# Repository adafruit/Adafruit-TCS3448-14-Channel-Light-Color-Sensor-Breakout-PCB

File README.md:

## Adafruit TCS3448 14-Channel Light / Color Sensor Breakout - STEMMA QT / Qwiic PCB

<a href="http://www.adafruit.com/products/6525"><br/>
Click here to purchase one from the Adafruit shop</a>

PCB files for the Adafruit TCS3448 14-Channel Light / Color Sensor Breakout - STEMMA QT / Qwiic. 

Format is EagleCAD schematic and board layout
* https://www.adafruit.com/product/6525

### Description

The <b>Adafruit TCS3448 (a.k.a TCS34488) Multi-Spectral Sensor</b> is a multi-channel spectrometer, which is a special type of light sensor that is able to detect not only the amount of light present but also the amounts of light within different wavelengths. This means that you can use it to detect much better than the human eye is capable of, what color or colors of light is present.

The TCS3448 packs within its 3x2mm footprint 25 photodiodes that can detect 11 separate, overlapping bands of visible light, plus one near infrared, one clear and a flicker channel for 14 channels total. Compared to the AS7341, this sensor has 4 more light channels - but you'll need to use a new firmware driver since it's not back-compatible.

<b>The TCS3448 is ams Osram's 'refresh' of the AS7343</b>, so it's an upgrade from the AS7341 and has some slight improvements/changes over the AS7343: 

* I2C address changed from 0x39 to 0x59.
* Retuned optical filters: channel centers move by a few nanometers and several visible channels have higher responsivity especially violet/blue and the F8 far-red channel.
* Sensitivity is not higher everywhere; NIR response is lower.
* Firmware is not 100% drop-in! You'll need to recompile since the I2C address has changed

The multi-spectral color measuring capabilities of the TCS3448 can be used to quantify the specific makeup of light, either emitted or reflective. It's kind of like a mini spectroscopy sensor. This is possible thanks to the impressive collection of sensors in the TCS3448 being routed through 6 independent 16-bit ADCs that take the raw measurements and convert them to digital values that can be read out over I2C.

14 readable individual sensor elements (13 light channels plus flicker detection) don’t exactly fit through a 6-channel ADC all at once, so the chip includes a so-called Super MUX (SMUX) that allows you to route the signal from any sensor to any ADC channel. The sensor also has GPIO and interrupt pins that can allow it to communicate directly with other sensors, or the microcontroller itself.

All of this capability is made accessible by mounting the sensor on a STEMMA QT form factor breakout board, complete with level shifting circuitry and [SparkFun Qwiic](https://www.sparkfun.com/qwiic) compatible [Stemma QT](https://learn.adafruit.com/introducing-adafruit-stemma-qt) connectors. This means that you can, without needing to solder, connect our TCS3448 breakout into your 3.3V or 5V microcontroller of choice be it an Arduino Uno, Raspberry Pi, or one of the many [CircuitPython-compatible boards](https://circuitpython.org/downloads). While it certainly takes a bit of work to make all those different light sensors share their measurements, our Arduino and CircuitPython libraries take care of all of that hard work for you and even include example code to help get you started. [QT Cable is not included, but we have a variety in the shop](https://www.adafruit.com/?q=stemma+qt+cable&sort=BestMatch).

### License

Adafruit invests time and resources providing this open source design, please support Adafruit and open-source hardware by purchasing products from [Adafruit](https://www.adafruit.com)!

Designed by Limor Fried/Ladyada for Adafruit Industries.

Creative Commons Attribution/Share-Alike, all text above must be included in any redistribution. 
See license.txt for additional details.

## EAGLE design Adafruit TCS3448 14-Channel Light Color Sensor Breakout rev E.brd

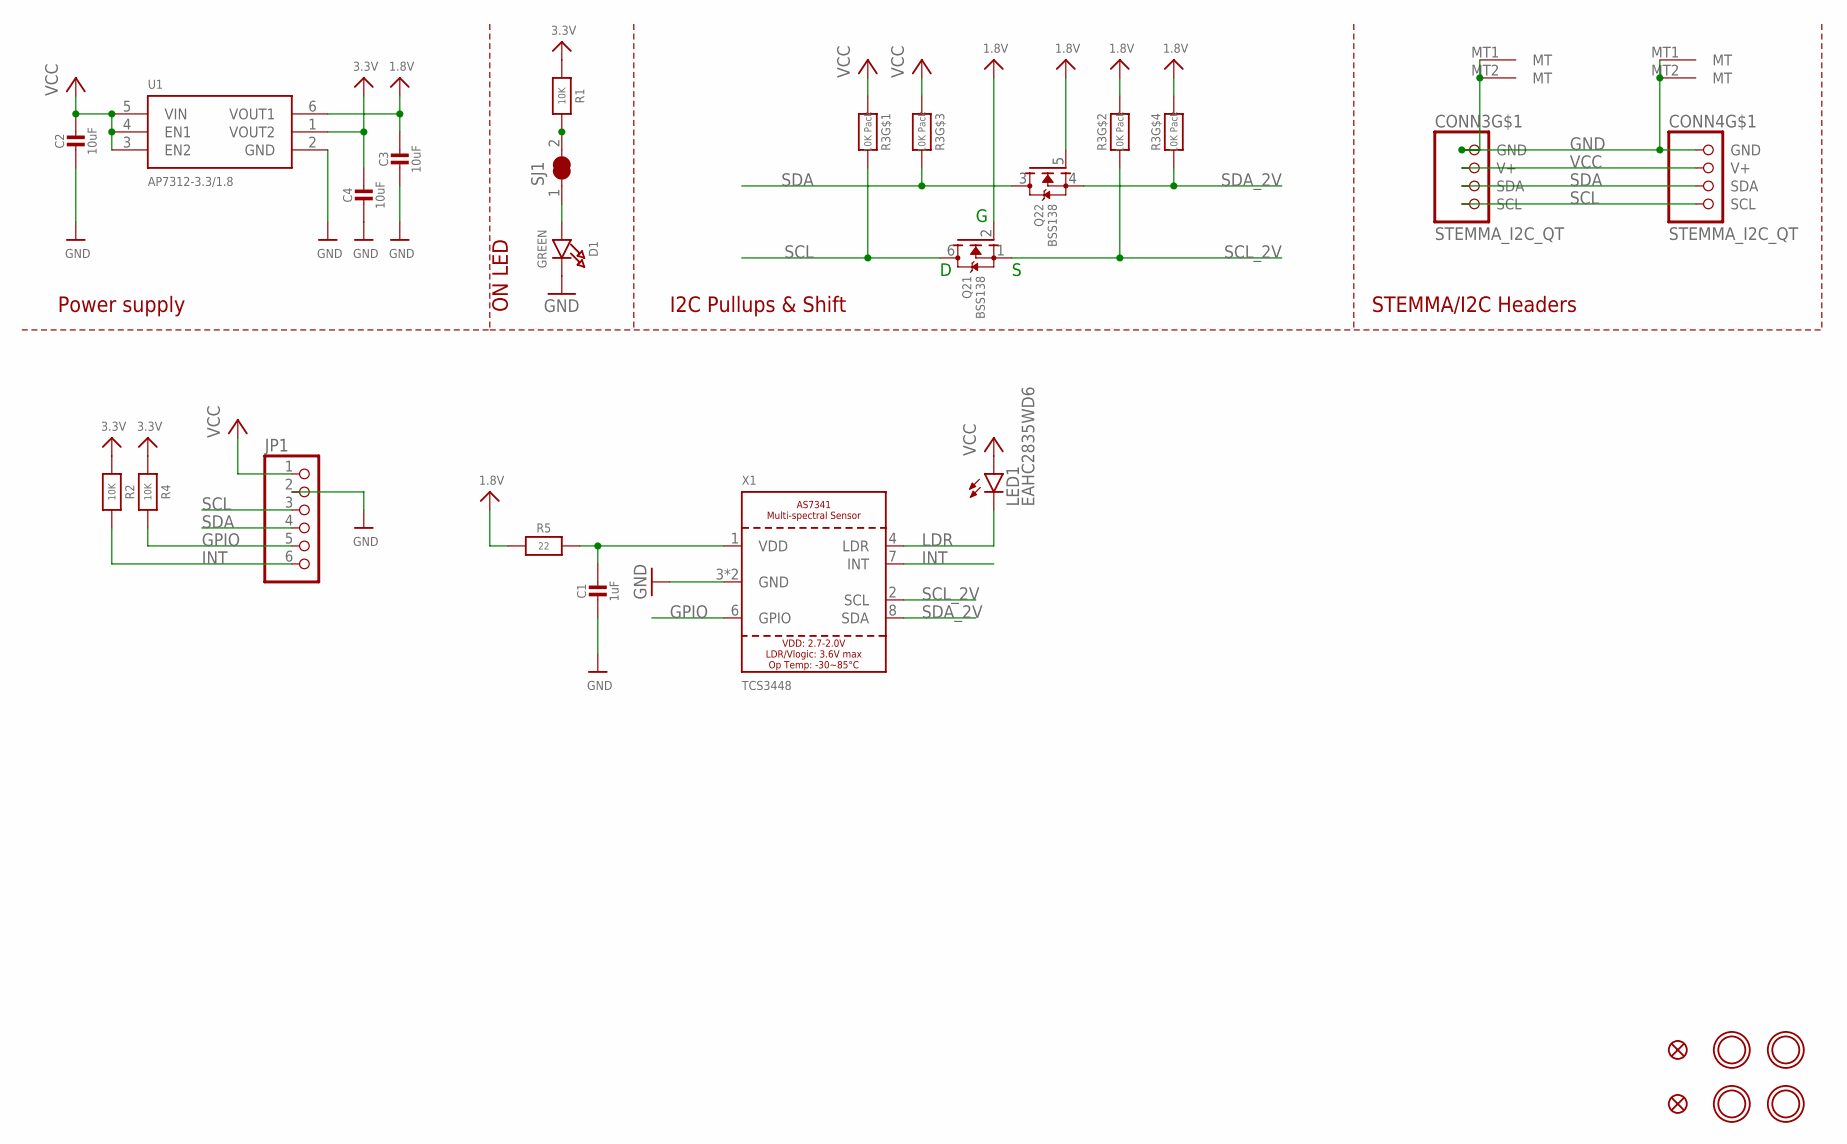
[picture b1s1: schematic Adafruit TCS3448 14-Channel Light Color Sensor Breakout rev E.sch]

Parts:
C1: 1uF; 0603-NO
C2, C3, C4: 10uF; 0805-NO
CONN3, CONN4: STEMMA_I2C_QT; JST_SH4
D1: GREEN; CHIPLED_0603_NOOUTLINE
FID3, FID4: FIDUCIAL_0.5MM
JP1: HEADER-1X670MIL; 1X06_ROUND_70
LED1: EAHC2835WD6; KA-3528ASYC
Q2: BSS138; SOT363
R1, R2, R4: 10K; 0603-NO
R3: 10K Pack; RESPACK_4X0603
R5: 22; 0603-NO
SJ1: SOLDERJUMPER_CLOSED; SOLDERJUMPER_CLOSEDWIRE
U1: AP7312-3.3/1.8; SOT23-6
U$1, U$17, U$19, U$21: MOUNTINGHOLE2.5; MOUNTINGHOLE_2.5_PLATED
X1: TCS3448; AS7341

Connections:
1.8V: C3.1, Q2.2 (G), Q2.5 (G), R3.2 (1), R3.4 (1), R5.1, U1.6 (VOUT1)
3.3V: C4.1, R1.1, R2.1, R4.1, U1.1 (VOUT2)
GND: C1.2, C2.2, C3.2, C4.2, CONN3.1 (GND), CONN3.MT1 (MT), CONN3.MT2 (MT), CONN4.1 (GND), CONN4.MT1 (MT), CONN4.MT2 (MT), D1.C, JP1.2, U1.2 (GND), X1.3 (GND), X1.5 (GND)
GPIO: JP1.5, R4.2, X1.6 (GPIO)
INT: JP1.6, R2.2, X1.7 (INT)
LDR: LED1.C, X1.4 (LDR)
unnamed: D1.A, SJ1.1
unnamed: R1.2, SJ1.2
unnamed: C1.1, R5.2, X1.1 (VDD)
SCL: CONN3.4 (SCL), CONN4.4 (SCL), JP1.3, Q2.6 (D), R3.8 (2)
SCL_2V: Q2.1 (S), R3.7 (2), X1.2 (SCL)
SDA: CONN3.3 (SDA), CONN4.3 (SDA), JP1.4, Q2.3 (D), R3.6 (2)
SDA_2V: Q2.4 (S), R3.5 (2), X1.8 (SDA)
VCC: C2.1, CONN3.2 (V+), CONN4.2 (V+), JP1.1, LED1.A, R3.1, R3.3 (1), U1.3 (EN2), U1.4 (EN1), U1.5 (VIN)

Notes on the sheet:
I2C Pullups & Shift
STEMMA/I2C Headers
ON LED
Power supply

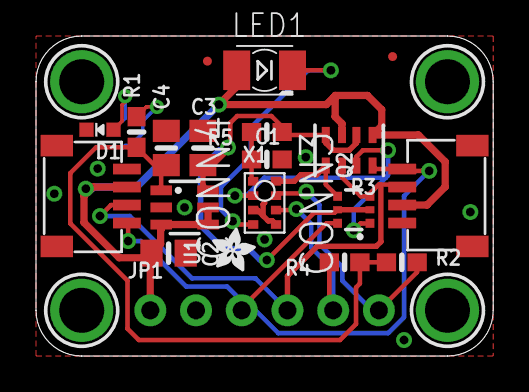
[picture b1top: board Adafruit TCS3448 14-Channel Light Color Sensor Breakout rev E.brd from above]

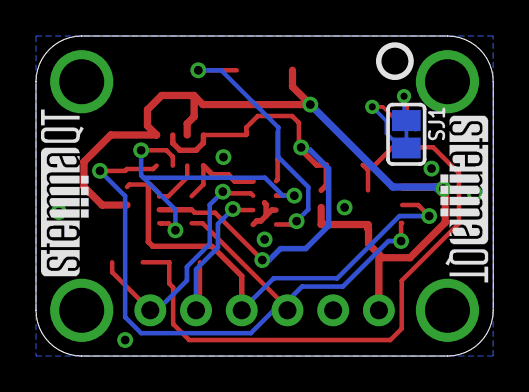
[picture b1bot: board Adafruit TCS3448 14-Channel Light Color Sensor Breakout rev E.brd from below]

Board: 2 copper layers, 25.4 x 17.8 mm, 44 parts (10 on the bottom side), 14 nets.

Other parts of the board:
PLABEL0: PLABEL0
PLABEL1: PLABEL1
PLABEL2: PLABEL2
PLABEL3: PLABEL3
PLABEL4: PLABEL4
PLABEL5: PLABEL5
PLABEL8: PLABEL8
PLABEL11: PLABEL11
PLABEL14: PLABEL14
PLABEL15: PLABEL15
PLABEL18: PLABEL18
PLABEL19: PLABEL19
PLABEL20: PLABEL20
PLABEL21: PLABEL21
PLABEL22: PLABEL22
PLABEL23: PLABEL23
U$16: ADAFRUIT_2.5MM
U$25: PCBFEAT-REV-040
U$30, U$31: STEMMAQT

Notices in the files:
parts and their libraries:
microbuilder: This work is placed in the public domain, and may be freely used for commercial and non-commercial work with the following conditions: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
